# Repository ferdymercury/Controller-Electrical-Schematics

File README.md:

_This repo is a part of the Hitchco MK4 project. You can read more about the project [here](http://www.esologic.com/hitchco-mk4/)._

# Controller-Electrical-Schematics

The PCB was designed in [KiCAD](http://kicad.org/) and manufactured by [OSHPark](https://oshpark.com/). It's essentially a giant shield for an Arduino Mega that drives many Power MOSFET devices, and conditions the inputs from the car. It also has many connectors for illuminated pushbuttons.

Many through-hole components were used for ease of assembly, and overall design simplicity.

The following diagram describes how signals are moved through the system:

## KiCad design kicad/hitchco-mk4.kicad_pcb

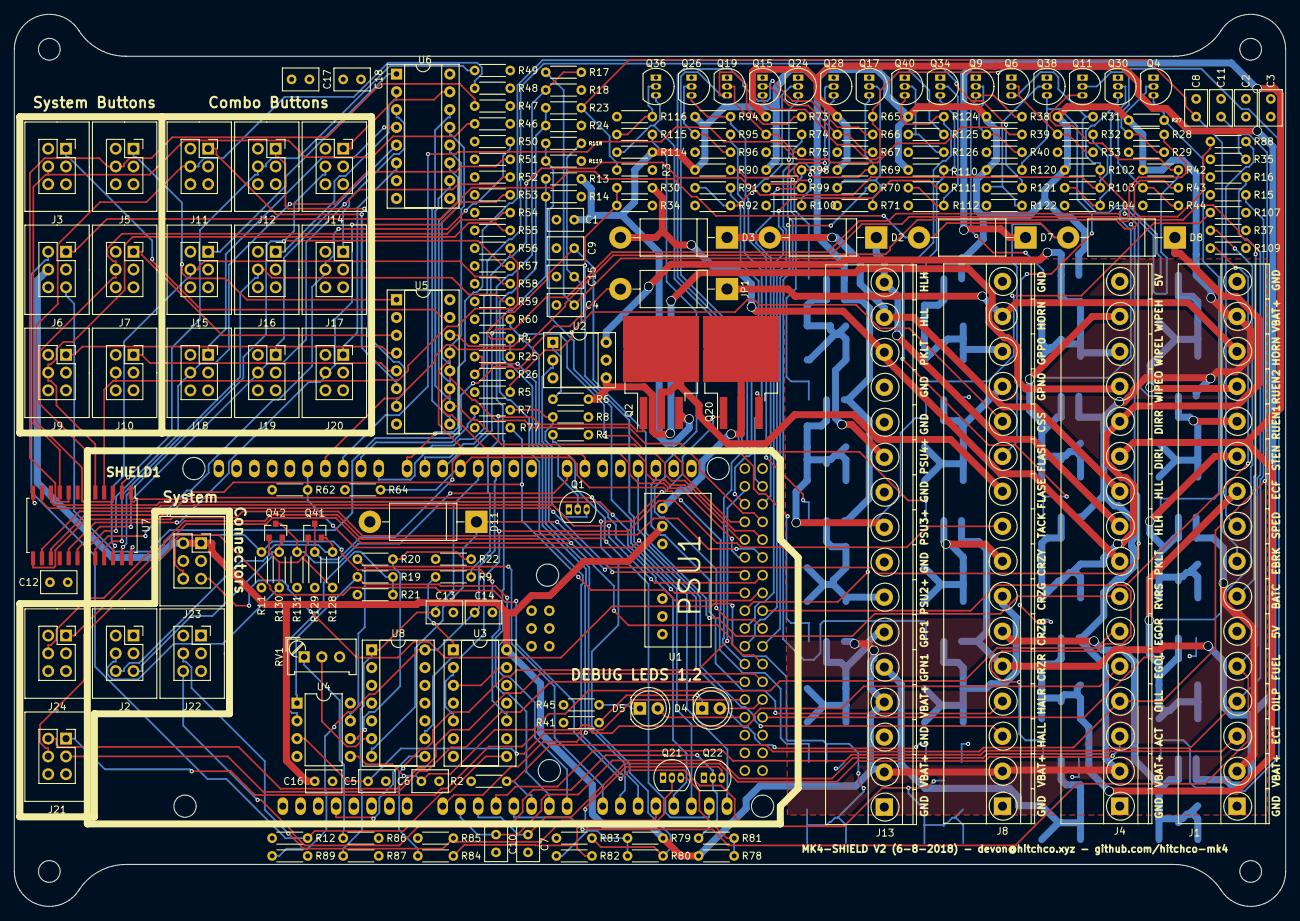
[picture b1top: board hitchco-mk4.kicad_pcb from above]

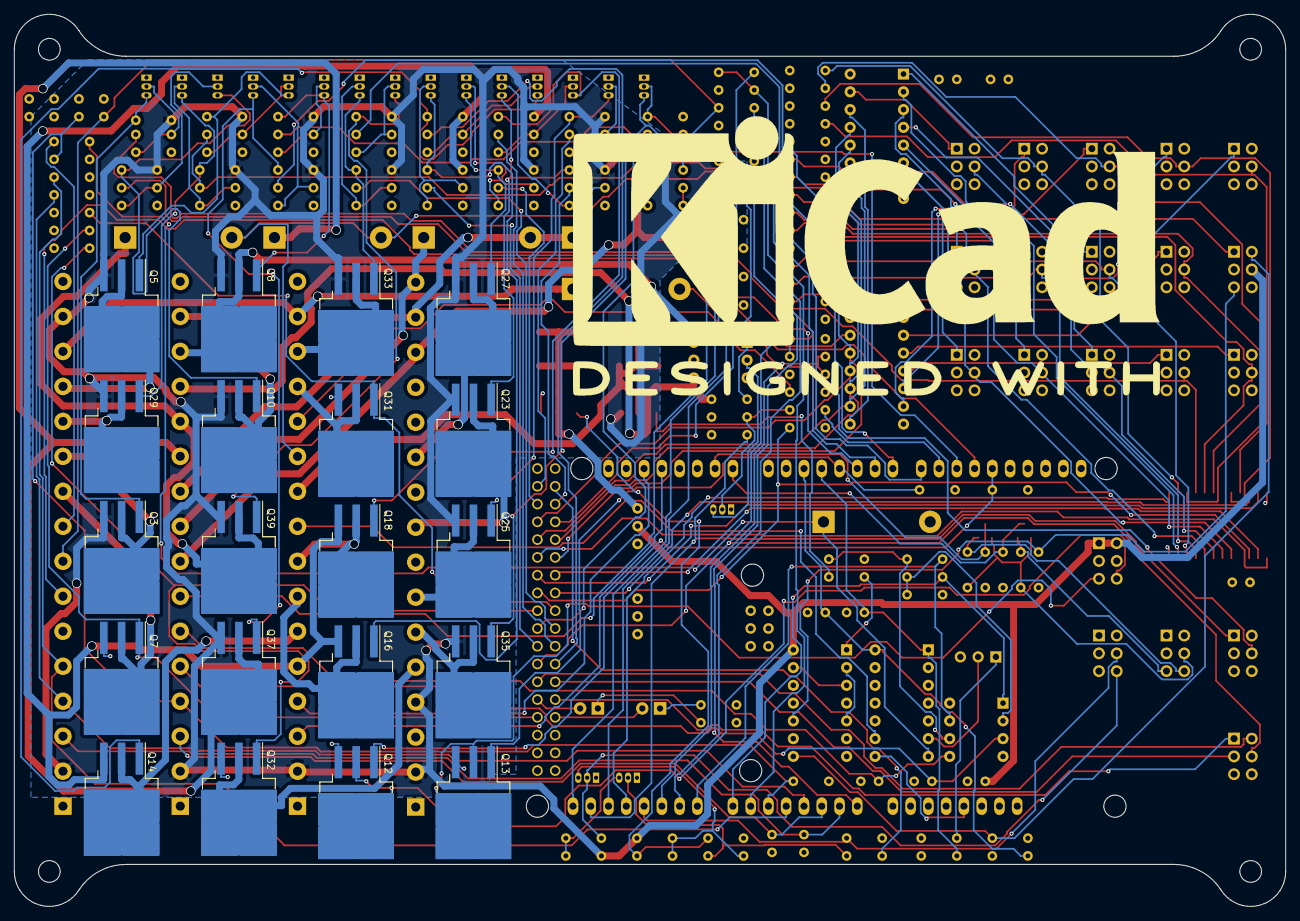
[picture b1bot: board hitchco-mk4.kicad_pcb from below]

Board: 4 copper layers, 181.7 x 127.5 mm, 216 parts (20 on the bottom side), 184 nets.

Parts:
C1, C2, C3, C4, C7, C8, C9, C10, C11, C12, C13, C14, C15, C16, C17, C18: 0.1uF; C_Rect_L5.08mm_W3.175mm_P2.54mm
C5, C6: 0.01uF; C_Rect_L5.08mm_W3.175mm_P2.54mm
D2, D3, D7, D8, D11: SB5100E-G; D_DO-201AD_P15.24mm_Horizontal
D4, D5: WP7113ID; LED_D5.0mm
J1, J4, J8, J13: Screw_Terminal_01x16; TerminalBlock_Phoenix_45Deg_MKDS1.5-16pol
J2, J3, J5, J6, J7, J9, J10, J11, J12, J14, J15, J16, J17, J18, J19, J20, J21, J22, J23, J24: Conn_02x03_Counter_Clockwise; Shroud_Socket_Strip_Straight_2x03_Pitch2.54mm
JP1: Jumper; D_DO-201AD_P15.24mm_Horizontal
Q1, Q4, Q6, Q9, Q11, Q15, Q17, Q19, Q21, Q22, Q24, Q26, Q28, Q30, Q34, Q36, Q38, Q40: 2N3904; TO-92_Inline_Narrow_Oval
Q2, Q3, Q5, Q8, Q10, Q14, Q16, Q18, Q23, Q25, Q27, Q29, Q33, Q35, Q37, Q39: NTB5605PT4G; TO-263-3_TabPin2
Q7, Q12, Q13, Q20, Q31, Q32: FQB30N06LTM; TO-263-3_TabPin2
Q41, Q42: BSS138; SOT-23
R1, R8, R9, R19, R20, R27, R29, R30, R31, R33, R35, R37, R38, R40, R42, R44, R62, R64, R65, R67, R69, R71, R73, R75, R77, R80, R81, R82, R83, R84, R85, R87, R88, R89, R90, R92, R94, R96, R98, R100, R102, R104, R107, R109, R110, R112, R114, R116, R120, R122, R124, R126, R128, R129, R130, R131: 10KΩ; R_Axial_DIN0204_L3.6mm_D1.6mm_P5.08mm_Horizontal
R2, R3, R4, R5, R7, R11, R12, R28, R32, R39, R43, R66, R70, R74, R91, R95, R99, R103, R111, R115, R121, R125: 1KΩ; R_Axial_DIN0204_L3.6mm_D1.6mm_P5.08mm_Horizontal
R6: 560Ω; R_Axial_DIN0204_L3.6mm_D1.6mm_P5.08mm_Horizontal
R13, R17, R23, R25, R118: 100KΩ; R_Axial_DIN0204_L3.6mm_D1.6mm_P5.08mm_Horizontal
R14, R24, R26, R119: 51KΩ; R_Axial_DIN0204_L3.6mm_D1.6mm_P5.08mm_Horizontal
R15: 43Ω; R_Axial_DIN0204_L3.6mm_D1.6mm_P5.08mm_Horizontal
R16: 47Ω; R_Axial_DIN0204_L3.6mm_D1.6mm_P5.08mm_Horizontal
R18: 105KΩ; R_Axial_DIN0204_L3.6mm_D1.6mm_P5.08mm_Horizontal
R21, R22: 4.3KΩ; R_Axial_DIN0204_L3.6mm_D1.6mm_P5.08mm_Horizontal
R34: 5.1KΩ; R_Axial_DIN0204_L3.6mm_D1.6mm_P5.08mm_Horizontal
R41, R45: 330Ω; R_Axial_DIN0204_L3.6mm_D1.6mm_P5.08mm_Horizontal
R46, R47, R48, R49, R50, R51, R52, R53, R54, R55, R56, R57, R58, R59, R60: 10K; R_Axial_DIN0204_L3.6mm_D1.6mm_P5.08mm_Horizontal
R78, R79: 3.3KΩ; R_Axial_DIN0204_L3.6mm_D1.6mm_P5.08mm_Horizontal
R86: 15KΩ; R_Axial_DIN0204_L3.6mm_D1.6mm_P5.08mm_Horizontal
RV1: 10KΩ; Potentiometer_Trimmer_Bourns_PV36W
SHIELD1: ARDUINO_MEGA_SHIELD
U1: NCS3S1205SC
U2: LCA715; DIP-6_W7.62mm_Socket
U3: CD4013B; DIP-14_W7.62mm_Socket
U4: LM358; DIP-8_W7.62mm
U5, U6: SN74HC595N; DIP-16_W7.62mm_Socket
U7: CD74HC4067; SOIC-24W_7.5x15.4mm_Pitch1.27mm
U8: LM339; DIP-14_W7.62mm_Socket

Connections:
3V3: SHIELD1.3V3, U8.8
/5V: C2.1, C3.1, C12.1, C17.1, C18.1, J1.6, J3.5, J4.16, J5.5, J7.5, J9.5, J10.5, J11.5, J12.5, J14.5, J15.5, J16.5, J17.5, J18.5, J19.5, J20.5, J21.5, J21.6, J24.2, J24.3, R2.1, R3.1, R4.1, R5.1, R15.1, R16.1, R35.2, R85.2, R86.1, R87.1, R89.1, R129.1, R131.1, SHIELD1.5V, SHIELD1.5V_4, SHIELD1.5V_5, U1.6, U4.8, U5.16, U6.16, U7.24, U8.3
/BATC: C4.1, J1.7, R17.1
/CRZB: J8.6, Q14.2
/CRZG: J8.7, Q16.2
/CRZR: J8.5, Q14.3, Q16.3, Q18.3, R65.1, R69.1, R73.1
/CRZY: J8.8, Q18.2
/CSS: C15.1, J8.12, R5.2, R118.1
/DIRL: D7.1, J4.11, Q37.2
/DIRR: D8.1, J4.12, Q39.2
/EBRK: C8.1, J1.8, R3.2, R23.1
/ECF: J1.10, Q7.2
/EGOL: C5.1, J4.5, U4.3
/EGOR: C6.1, J4.6, U4.5
/FLASHEN: J8.10, Q2.2
/FLASHIN: D7.2, D8.2, J6.1, J8.11
/GND: C1.2, C2.2, C3.2, C4.2, C5.2, C6.2, C7.2, C8.2, C9.2, C10.2, C11.2, C12.2, C13.2, C14.2, C15.2, C16.1, C17.2, C18.2, D11.2, J1.1, J1.16, J2.1, J3.6, J4.1, J5.6, J6.6, J7.6, J8.1, J8.16, J9.6, J10.6, J11.6, J12.6, J13.1, J13.3, J13.8, J13.10, J13.12, J13.13, J14.6, J15.6, J16.6, J17.6, J18.6, J19.6, J20.6, J22.5, Q1.1, Q4.1, Q6.1, Q7.3, Q9.1, Q11.1, Q12.3, Q13.3, Q15.1, Q17.1, Q19.1, Q20.3, Q21.1, Q22.1, Q24.1, Q26.1, Q28.1, Q30.1, Q31.3, Q32.3, Q34.1, Q36.1, Q38.1, Q40.1, R1.1, R8.1, R11.2, R12.2, R14.2, R18.2, R21.1, R22.1, R24.2, R26.2, R29.1, R33.1, R34.2, R37.2, R40.1, R41.2, R44.1, R45.2, R46.1, R47.1, R48.1, R49.1, R50.1, R51.1, R52.1, R53.1, R54.1, R55.1, R56.1, R57.1, R58.1, R59.1, R60.1, R62.2, R64.2, R67.1, R71.1, R75.1, R77.2, R83.2, R92.1, R96.1, R100.1, R104.1, R107.2, R109.2, R112.1, R116.1, R119.2, R122.1, R126.1, RV1.3, SHIELD1.GND1, SHIELD1.GND2, SHIELD1.GND4, SHIELD1.GND5, U1.7, U3.4, U3.6, U3.7, U3.9, U3.11, U4.4, U5.8, U6.8, U7.12, U8.12
/GPN0: J8.13, Q31.2
/GPN1: J13.5, Q32.2
/GPP0: J8.14, Q33.2
/GPP1: J13.6, Q35.2
/HALL: J8.3, SHIELD1.18
/HALR: J8.4, SHIELD1.19
/HLH: D2.1, J4.9, J13.16
/HLL: D2.2, D3.1, J4.10, J13.15
/HORN: J1.14, J8.15, JP1.1
/PKLT: D3.2, J4.8, J13.14, R30.1
/PSU2_12V: J13.7, Q25.2
/PSU3_12V: J13.9, Q23.2
/PSU4_12V: J13.11, Q27.2
/RUEN1: J1.12, Q29.2
/RUEN2: J1.13, Q5.2
/RVRS: C9.1, J4.7, R4.2, R25.1
/SPED: J1.9, R88.1
/STEN: J1.11, Q3.2
/TACK: J8.9, U8.9
/VBAT+: C1.1, C16.2, J1.2, J1.15, J4.2, J6.4, J8.2, J13.2, J13.4, J23.1, J23.2, Q2.3, Q3.3, Q5.3, Q8.3, Q10.3, Q23.3, Q25.3, Q27.3, Q29.3, Q33.3, Q35.3, Q37.3, Q39.3, R13.1, R27.1, R31.1, R38.1, R42.1, R78.1, R79.1, R90.1, R94.1, R98.1, R102.1, R110.1, R114.1, R120.1, R124.1, U1.2, U3.14
/WIPEH: J4.15, Q10.2
/WIPEL: J4.14, Q8.2, U2.6
/WIPEO: J4.13, R6.2, U2.4
/hitchco-mk4/LED1-: J23.6, Q12.2
/hitchco-mk4/LED2-: J23.5, Q13.2
/hitchco-mk4/PB3_NC: J6.2, R12.1, U3.8
/hitchco-mk4/PB3_NO: J6.5, R11.1, U3.10
/hitchco-mk4/PB5_LED-: J24.4, JP1.2
/hitchco-mk4/RPI3V3: J2.4, Q41.1, Q42.1, R128.1, R130.1
/hitchco-mk4/RPIRX: J2.5, Q42.2, R130.2
/hitchco-mk4/RPITX: J2.6, Q41.2, R128.2
/hitchco-mk4/RS1_L1: J22.6, Q22.2, R81.1
/hitchco-mk4/SoftPowerSwitch/GND_OUTPUT: Q20.2, U1.1
ACT_SIG_PIN: C7.1, J4.3, SHIELD1.AD2
BATC_SIG_PIN: R17.2, R18.1, SHIELD1.AD6
CLK1: U3.3, U3.13
CRZ_DISABLE_PIN: R66.2, SHIELD1.42
CRZ_MAINTAIN_PIN: R70.2, SHIELD1.41
CRZ_RESUME_PIN: R74.2, SHIELD1.40
CSS_SIG_PIN: R118.2, R119.1, SHIELD1.AD13
DIRL_EN_PIN: R121.2, SHIELD1.7
DIRR_EN_PIN: R125.2, SHIELD1.8
EBRK_SIG_PIN: R23.2, R24.1, SHIELD1.AD9
ECF_EN_PIN: Q7.1, R37.1, SHIELD1.49
ECT_SIG_PIN: C10.1, J1.3, SHIELD1.AD1
EGOL_SIG_PIN: R19.1, SHIELD1.AD7, U4.1
EGOR_SIG_PIN: R20.1, SHIELD1.AD8, U4.7
FUEL_SIG_PIN: J1.5, R16.2, SHIELD1.AD4
GPN0_EN_PIN: Q31.1, R107.1, SHIELD1.36
GPN1_EN_PIN: Q32.1, R109.1, SHIELD1.37
GPP0_EN_PIN: R111.2, SHIELD1.38
GPP1_EN_PIN: R115.2, SHIELD1.39
LDR_SIG_PIN: J24.1, R1.2, SHIELD1.AD14
LED1_EN_PIN: Q12.1, R62.1, SHIELD1.12
LED2_EN_PIN: Q13.1, R64.1, SHIELD1.4
LITE_SIG_PIN: R30.2, R34.1, SHIELD1.AD15
MUX_EN_PIN: R77.1, SHIELD1.35, U7.15
MUX_S0_PIN: SHIELD1.34, U7.10
MUX_S1_PIN: SHIELD1.33, U7.11
MUX_S2_PIN: SHIELD1.32, U7.14
MUX_S3_PIN: SHIELD1.31, U7.13
MUX_SIG_PIN: SHIELD1.AD12, U7.1
unnamed: D4.1, R41.1
unnamed: D4.2, SHIELD1.47
unnamed: D5.1, R45.1
unnamed: D5.2, SHIELD1.48
unnamed: D11.1, R88.2, U8.7
unnamed: Q1.2, R7.1, R8.2
unnamed: Q1.3, U2.2
unnamed: Q2.1, R9.2
unnamed: Q3.1, Q4.3, R27.2
unnamed: Q4.2, R28.1, R29.2
unnamed: Q5.1, Q6.3, R31.2
unnamed: Q6.2, R32.1, R33.2
unnamed: Q8.1, Q9.3, R38.2
unnamed: Q9.2, R39.1, R40.2
unnamed: Q10.1, Q11.3, R42.2
unnamed: Q11.2, R43.1, R44.2
unnamed: Q14.1, Q15.3, R65.2
unnamed: Q15.2, R66.1, R67.2
unnamed: Q16.1, Q17.3, R69.2
unnamed: Q17.2, R70.1, R71.2
unnamed: Q18.1, Q19.3, R73.2
unnamed: Q19.2, R74.1, R75.2
unnamed: Q20.1, R80.1, R83.1
unnamed: Q21.2, R82.2, R84.1
unnamed: Q21.3, R78.2, R81.2
unnamed: Q22.3, R79.2, R80.2, R82.1
unnamed: Q23.1, Q24.3, R90.2
unnamed: Q24.2, R91.1, R92.2
unnamed: Q25.1, Q26.3, R94.2
unnamed: Q26.2, R95.1, R96.2
unnamed: Q27.1, Q28.3, R98.2
unnamed: Q28.2, R99.1, R100.2
unnamed: Q29.1, Q30.3, R102.2
unnamed: Q30.2, R103.1, R104.2
unnamed: Q33.1, Q34.3, R110.2
unnamed: Q34.2, R111.1, R112.2
unnamed: Q35.1, Q36.3, R114.2
unnamed: Q36.2, R115.1, R116.2
unnamed: Q37.1, Q38.3, R120.2
unnamed: Q38.2, R121.1, R122.2
unnamed: Q39.1, Q40.3, R124.2
unnamed: Q40.2, R125.1, R126.2
unnamed: R6.1, U2.1
unnamed: R9.1, U3.1
unnamed: R19.2, R21.2, U4.2
unnamed: R20.2, R22.2, U4.6
unnamed: R86.2, RV1.1
unnamed: RV1.2, U8.6
unnamed: U3.2, U3.5
unnamed: U5.9, U6.14
OILL_SIG_PIN: C11.1, J4.4, R2.2, R35.1, SHIELD1.AD5
OILP_SIG_PIN: J1.4, R15.2, SHIELD1.AD3
PB1_LED_EN: J3.1, U5.15
PB1_SIG_PIN: J3.4, R46.2, U7.9
PB2_LED_EN: J5.1, U5.1
PB2_SIG_PIN: J5.4, R47.2, U7.8
PB4_LED_EN: J7.1, U5.3
PB4_SIG_PIN: J7.4, R54.2, U7.6
PB6_LED_EN: J9.1, U5.4
PB6_SIG_PIN: J9.4, R55.2, U7.5
PB7_LED_EN: J10.1, U5.5
PB7_SIG_PIN: J10.4, R56.2, U7.4
PB8_BLED_EN: J21.3, SHIELD1.44
PB8_GLED_EN: J21.2, SHIELD1.45
PB8_RLED_EN: J21.1, SHIELD1.46
PB8_SIG_PIN: J21.4, R60.2, SHIELD1.43
PB9_LED_EN: J11.1, U5.6
PB9_SIG_PIN: J11.4, R48.2, U7.3
PB10_LED_EN: J12.1, U5.7
PB10_SIG_PIN: J12.4, R49.2, U7.2
PB11_LED_EN: J14.1, U6.15
PB11_SIG_PIN: J14.4, R57.2, U7.23
PB12_LED_EN: J15.1, U6.1
PB12_SIG_PIN: J15.4, R58.2, U7.22
PB13_LED_EN: J16.1, U6.2
PB13_SIG_PIN: J16.4, R59.2, U7.21
PB14_LED_EN: J17.1, U6.3
PB14_SIG_PIN: J17.4, R50.2, U7.20
PB15_LED_EN: J18.1, U6.4
PB15_SIG_PIN: J18.4, R51.2, U7.19
PB16_LED_EN: J19.1, U6.5
PB16_SIG_PIN: J19.4, R52.2, U7.18
PB17_LED_EN: J20.1, U6.6
PB17_SIG_PIN: J20.4, R53.2, U7.17
PSU1_EN_PIN: R84.2, SHIELD1.22
PSU1_SIG_PIN: J22.4, R85.1, SHIELD1.AD11
PSU2_EN_PIN: R95.2, SHIELD1.23
PSU3_EN_PIN: R91.2, SHIELD1.24
PSU4_EN_PIN: R99.2, SHIELD1.25
RPI_RX: Q42.3, R131.2, SHIELD1.14
RPI_TX: Q41.3, R129.2, SHIELD1.15
RUEN_EN_PIN: R32.2, R103.2, SHIELD1.6
RVRS_SIG_PIN: R25.2, R26.1, SHIELD1.AD10
SPED_SIG_PIN: C13.1, R87.2, SHIELD1.3, U8.1
SREG_OE_PIN: SHIELD1.30, U5.13, U6.13
SREG_RCLK_PIN: SHIELD1.27, U5.12, U6.12
SREG_SER_PIN: SHIELD1.26, U5.14
SREG_SRCLK_PIN: SHIELD1.28, U5.11, U6.11
SREG_SRCLR_PIN: SHIELD1.29, U5.10, U6.10
STEN_EN_PIN: R28.2, SHIELD1.5
TACK_SIG_PIN: C14.1, R89.2, SHIELD1.2, U8.14
VBAT_SIG_PIN: R13.2, R14.1, SHIELD1.AD0
WIPEH_EN_PIN: R43.2, SHIELD1.11
WIPEL_EN_PIN: R39.2, SHIELD1.10
WIPEO_EN_PIN: R7.2, SHIELD1.9

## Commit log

2018-04-18 adding files
2018-04-27 added multiple folders for both versions
2018-05-04 Soft push of v2 board modifications
2018-05-20 working through adding new features
2018-05-22 got most of the screw terminals planned out in schem
2018-05-23 added headnight diodes, I don't think software control of them is going to be possible
2018-06-02 schematic is done, footprint association and netlist are also done
2018-06-05 all components on the board
2018-06-06 before ar
2018-06-09 all files are in, time to order!
2018-07-02 images up
2018-07-02 adding pdf
2018-07-02 moved images in readme
2021-11-10 Update README.md
    https://forum.kicad.info/t/warning-avoid-all-links-to-kicad-pcb-org-use-kicad-org/31521
